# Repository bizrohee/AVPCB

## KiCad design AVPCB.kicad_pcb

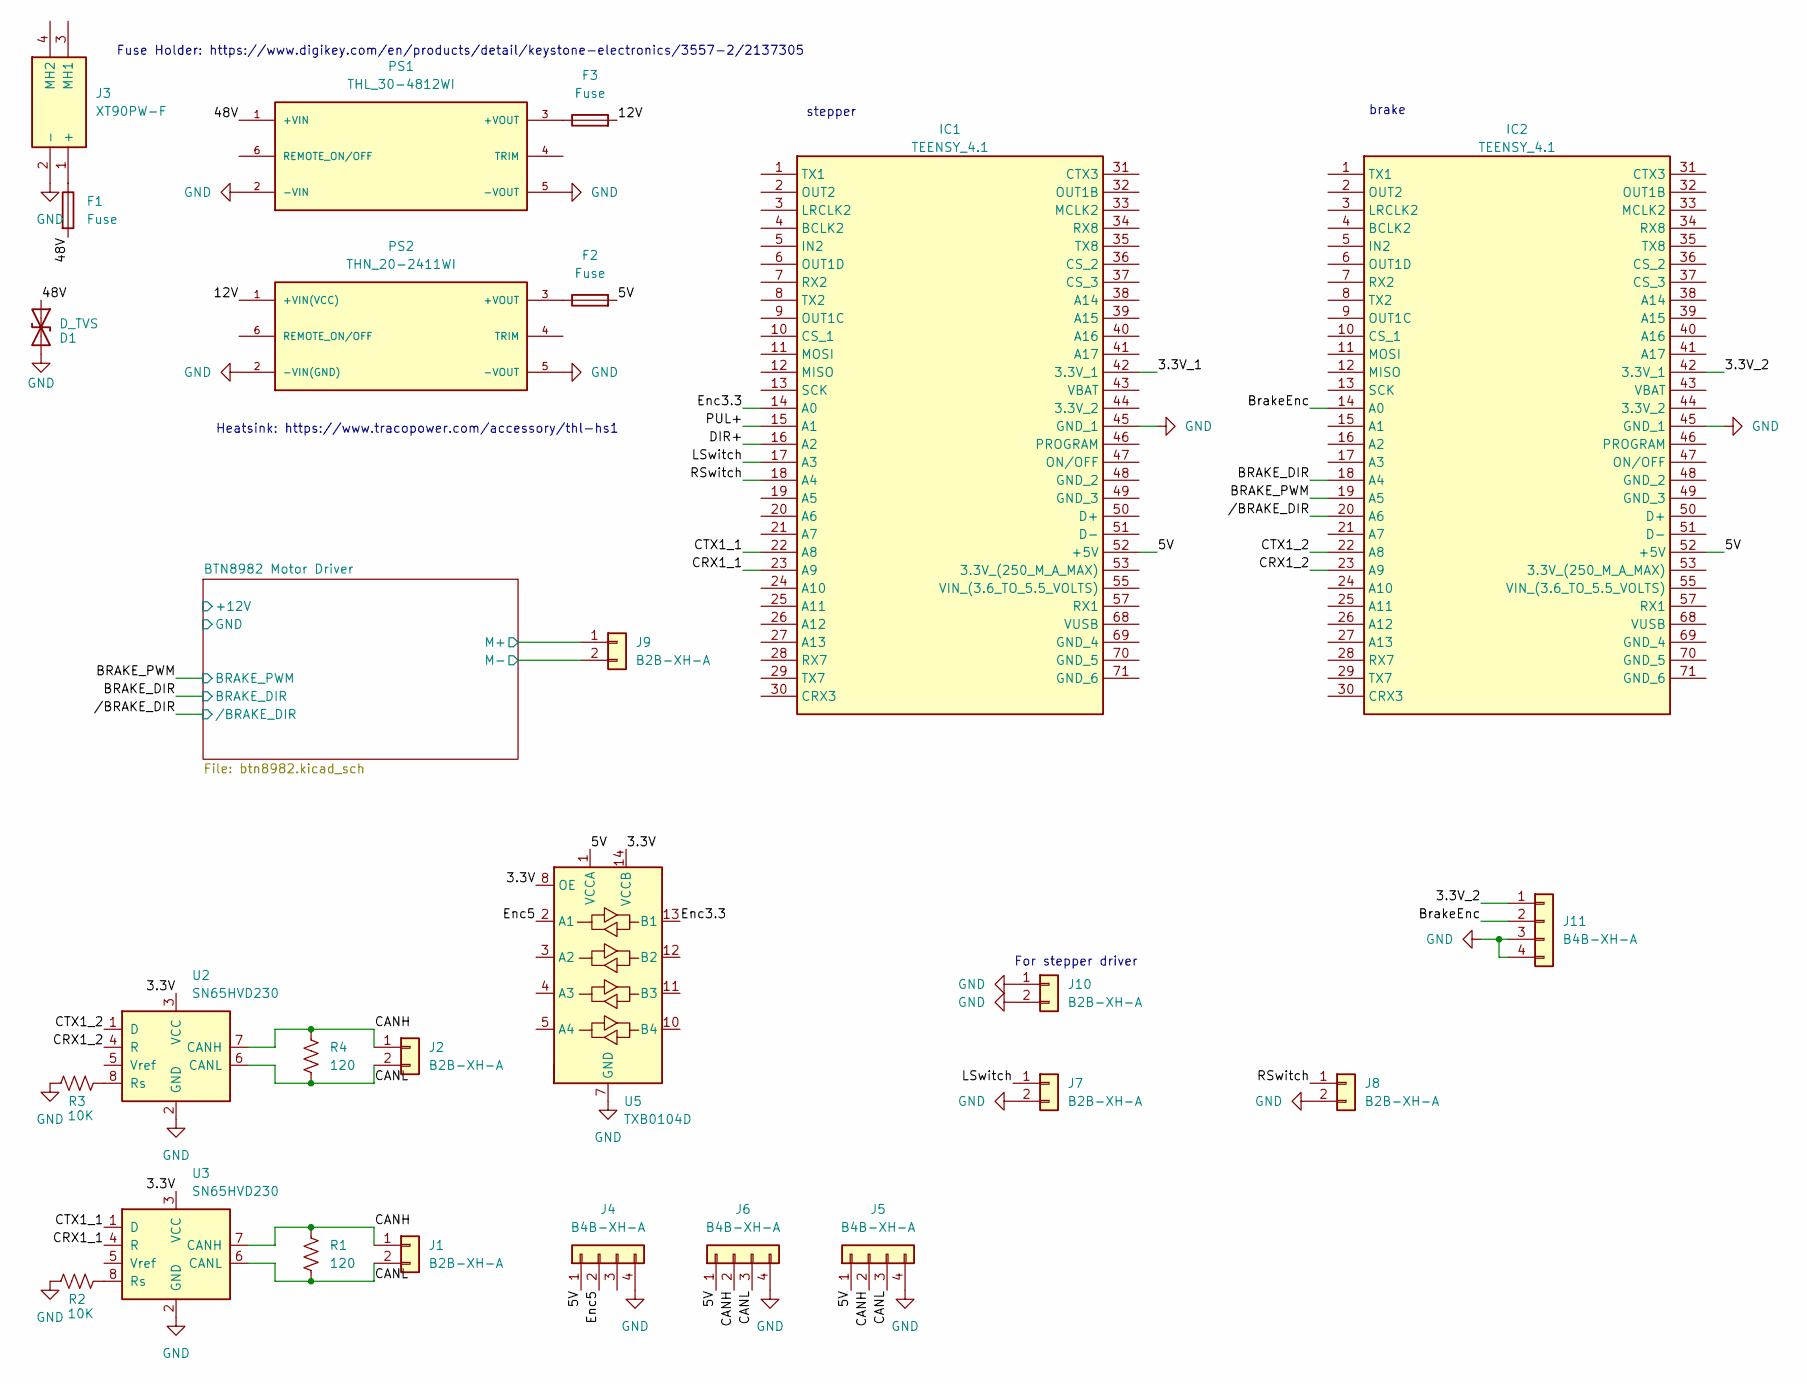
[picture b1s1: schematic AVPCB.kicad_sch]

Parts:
D1: D_TVS; D_0805_2012Metric_Pad1.15x1.40mm_HandSolder
F1, F2, F3: Fuse; 3557-2
IC1, IC2: TEENSY_4.1; TEENSY41; Manufacturer_Part_Number TEENSY 4.1
J1, J2, J7, J8, J9, J10: B2B-XH-A; B2BXHA
J3: XT90PW-F; XT90PWF; Manufacturer_Part_Number XT90PW-F
J4, J5, J6, J11: B4B-XH-A; B4BXHA
PS1: THL_30-4812WI; THL304812WI; PARTREV October 26, 2022
PS2: THN_20-2411WI; THN_20WI_SERIES; PARTREV March 16, 2021
R1, R4: 120; R_0805_2012Metric_Pad1.20x1.40mm_HandSolder
R2, R3: 10K; R_0805_2012Metric_Pad1.20x1.40mm_HandSolder
U2, U3: SN65HVD230; SOIC-8_3.9x4.9mm_P1.27mm
U5: TXB0104D; SOIC-14_3.9x8.7mm_P1.27mm

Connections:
/3.3V: U2.3 (VCC), U3.3 (VCC), U5.8 (OE), U5.14 (VCCB)
/3.3V_1: IC1.42 (3.3V_1)
/3.3V_2: IC2.42 (3.3V_1), J11.1
/5V: F2.2, IC1.52 (+5V), IC2.52 (+5V), J4.1, J5.1, J6.1, U5.1 (VCCA)
/12V: F3.2, PS2.1 (+VIN(VCC))
/48V: D1.1 (A1), F1.2, PS1.1 (+VIN)
/BRAKE_DIR: IC2.18 (A4); also elsewhere on the board
/BRAKE_PWM: IC2.19 (A5); also elsewhere on the board
/BTN8982 Motor Driver/M+: J9.1; also elsewhere on the board
/BTN8982 Motor Driver/M-: J9.2; also elsewhere on the board
/BrakeEnc: IC2.14 (A0), J11.2
/CANH: J1.1, J2.1, J5.2, J6.2, R1.1, R4.1, U2.7 (CANH), U3.7 (CANH)
/CANL: J1.2, J2.2, J5.3, J6.3, R1.2, R4.2, U2.6 (CANL), U3.6 (CANL)
/CRX1_1: IC1.23 (A9), U3.4 (R)
/CRX1_2: IC2.23 (A9), U2.4 (R)
/CTX1_1: IC1.22 (A8), U3.1 (D)
/CTX1_2: IC2.22 (A8), U2.1 (D)
/DIR+: IC1.16 (A2)
/Enc3.3: IC1.14 (A0), U5.13 (B1)
/Enc5: J4.2, U5.2 (A1)
/LSwitch: IC1.17 (A3), J7.1
/PUL+: IC1.15 (A1)
/RSwitch: IC1.18 (A4), J8.1
//BRAKE_DIR: IC2.20 (A6); also elsewhere on the board
GND: D1.2 (A2), IC1.45 (GND_1), IC2.45 (GND_1), J3.2 (-), J4.4, J5.4, J6.4, J7.2, J8.2, J10.1, J10.2, J11.3, J11.4, PS1.2 (-VIN), PS1.5 (-VOUT), PS2.2 (-VIN(GND)), PS2.5 (-VOUT), R2.1, R3.1, U2.2 (GND), U3.2 (GND), U5.7 (GND); also elsewhere on the board
unnamed: F1.1, J3.1 (+)
unnamed: F3.1, PS1.3 (+VOUT)
unnamed: F2.1, PS2.3 (+VOUT)
unnamed: R3.2, U2.8 (Rs)
unnamed: R2.2, U3.8 (Rs)

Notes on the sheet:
For stepper driver
stepper
brake
Fuse Holder: https://www.digikey.com/en/products/detail/keystone-electronics/3557-2/2137305
Heatsink: https://www.tracopower.com/accessory/thl-hs1

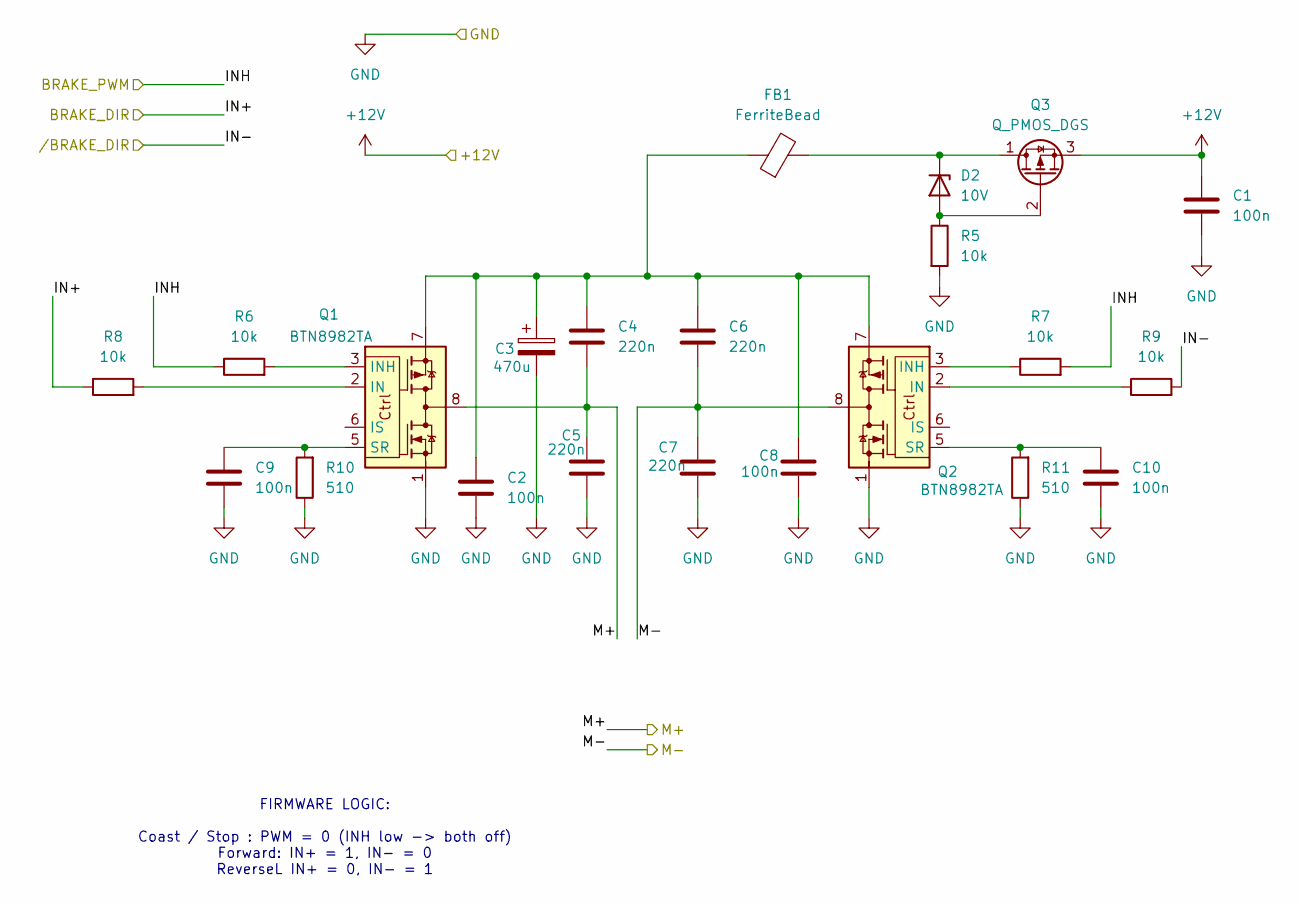
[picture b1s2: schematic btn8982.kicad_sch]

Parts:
C1, C2, C8, C9, C10: 100n; C_0805_2012Metric_Pad1.18x1.45mm_HandSolder
C3: 470u; CP_Radial_D10.0mm_P5.00mm
C4, C5, C6, C7: 220n; C_0805_2012Metric_Pad1.18x1.45mm_HandSolder
D2: 10V; D_0805_2012Metric_Pad1.15x1.40mm_HandSolder
FB1: FerriteBead; LairdTech_28C0236-0JW-10
Q1, Q2: BTN8982TA; TO-263-7_TabPin8
Q3: Q_PMOS_DGS; SI2305TP
R5, R6, R7, R8, R9: 10k; R_0805_2012Metric_Pad1.20x1.40mm_HandSolder
R10, R11: 510; R_0805_2012Metric_Pad1.20x1.40mm_HandSolder

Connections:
+12V: C1.1, Q3.3 (S)
/BRAKE_DIR: R8.1; also elsewhere on the board
/BRAKE_PWM: R6.1, R7.2; also elsewhere on the board
/BTN8982 Motor Driver/M+: C4.2, C5.1, Q1.4, Q1.8; also elsewhere on the board
/BTN8982 Motor Driver/M-: C6.2, C7.1, Q2.4, Q2.8; also elsewhere on the board
//BRAKE_DIR: R9.2; also elsewhere on the board
GND: C1.2, C2.2, C3.2, C5.2, C7.2, C8.2, C9.2, C10.2, Q1.1, Q2.1, R5.2, R10.1, R11.1; also elsewhere on the board
unnamed: C2.1, C3.1, C4.1, C6.1, C8.1, FB1.1, Q1.7, Q2.7
unnamed: D2.2 (A), Q3.2 (G), R5.1
unnamed: D2.1 (K), FB1.2, Q3.1 (D)
unnamed: Q1.2 (IN), R8.2
unnamed: Q1.3 (INH), R6.2
unnamed: C9.1, Q1.5 (SR), R10.2
unnamed: Q2.2 (IN), R9.1
unnamed: Q2.3 (INH), R7.1
unnamed: C10.1, Q2.5 (SR), R11.2

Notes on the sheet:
FIRMWARE LOGIC: Coast / Stop : PWM = 0 (INH low -> both off) Forward: IN+ = 1, IN- = 0 ReverseL IN+ = 0, IN- = 1

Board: 2 copper layers, 48 parts (0 on the bottom side), 37 nets, no tracks yet.

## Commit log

2026-01-21 Initial commit: AVPCB KiCad project
2026-02-03 Update schematic
